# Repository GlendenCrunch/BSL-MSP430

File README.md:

# BSL MSP430 + ftdi-rs232
+ Scheme and PCB of the adapter USB-FTDI to interface RS-232 and bootloader (BSL) for microcontrollers Texas Instrument MSP430
+ Libraries Eagle: SparkFun
+ For MAX232CPE from China capacitor С6 = 48 uF, otherwise it is not needed
+ Package 3D:

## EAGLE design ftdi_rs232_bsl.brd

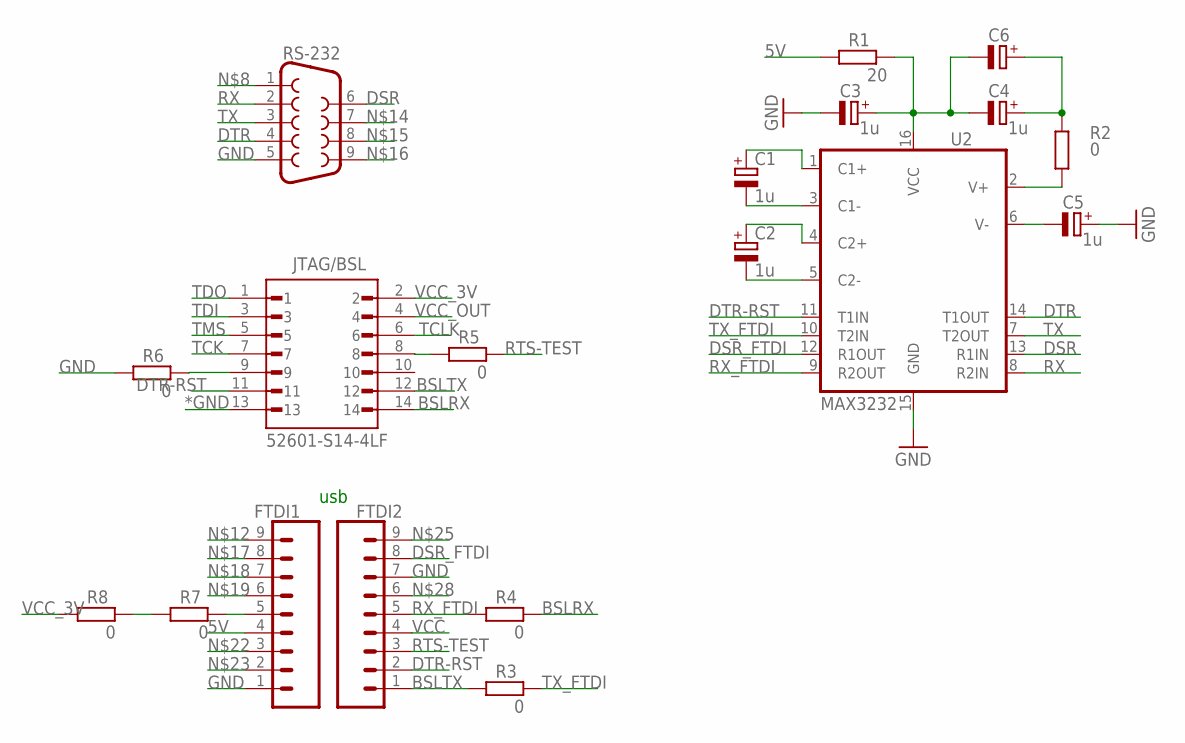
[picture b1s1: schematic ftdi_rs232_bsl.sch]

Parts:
C1, C2, C3, C4, C5: 1u; B/3528-21W
C6: CPOL-EUB/3528-21W; B/3528-21W
FTDI1, FTDI2: CONN_09NO_SILK; 1X09_NO_SILK
JTAG/BSL: 52601-S14-4LF; AMPHENOL_52601-S14-4LF
R1: 20; R1206
R2, R3, R4, R5, R6, R7, R8: 0; R1206
RS-232: DB9MALE; DB9_MALE
U2: MAX3232; DIP16

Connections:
5V: FTDI1.4, R1.1
*GND: JTAG/BSL.13
BSLRX: JTAG/BSL.14, R4.2
BSLTX: FTDI2.1, JTAG/BSL.12, R3.1
DSR: RS-232.6, U2.13 (R1IN)
DSR_FTDI: FTDI2.8, U2.12 (R1OUT)
DTR: RS-232.4, U2.14 (T1OUT)
DTR-RST: FTDI2.2, JTAG/BSL.11, U2.11 (T1IN)
GND: C3.-, C5.+, FTDI1.1, FTDI2.7, R6.1, RS-232.5, U2.15 (GND)
unnamed: C1.-, U2.3 (C1-)
unnamed: C2.-, U2.5 (C2-)
unnamed: C1.+, U2.1 (C1+)
unnamed: C2.+, U2.4 (C2+)
unnamed: C3.+, C4.-, C6.-, R1.2, U2.16 (VCC)
unnamed: C5.-, U2.6 (V-)
unnamed: C4.+, C6.+, R2.2
unnamed: R2.1, U2.2 (V+)
unnamed: JTAG/BSL.8, R5.1
unnamed: JTAG/BSL.9, R6.2
unnamed: FTDI1.5, R7.2
unnamed: R7.1, R8.2
RTS-TEST: FTDI2.3, R5.2
RX: RS-232.2, U2.8 (R2IN)
RX_FTDI: FTDI2.5, R4.1, U2.9 (R2OUT)
TCK: JTAG/BSL.7
TCLK: JTAG/BSL.6
TDI: JTAG/BSL.3
TDO: JTAG/BSL.1
TMS: JTAG/BSL.5
TX: RS-232.3, U2.7 (T2OUT)
TX_FTDI: R3.2, U2.10 (T2IN)
VCC: FTDI2.4
VCC_3V: JTAG/BSL.2, R8.1
VCC_OUT: JTAG/BSL.4

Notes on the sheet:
usb

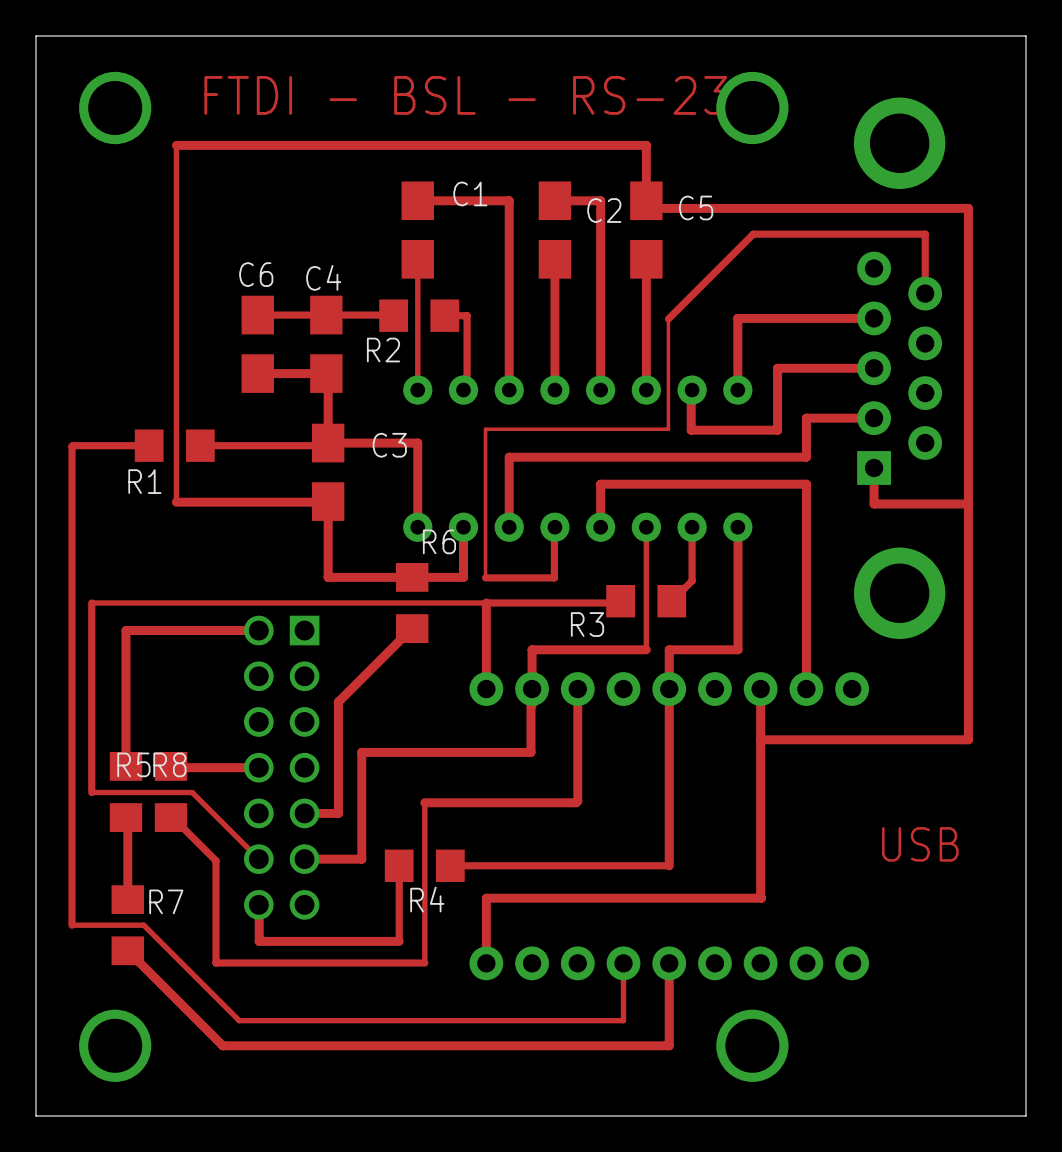
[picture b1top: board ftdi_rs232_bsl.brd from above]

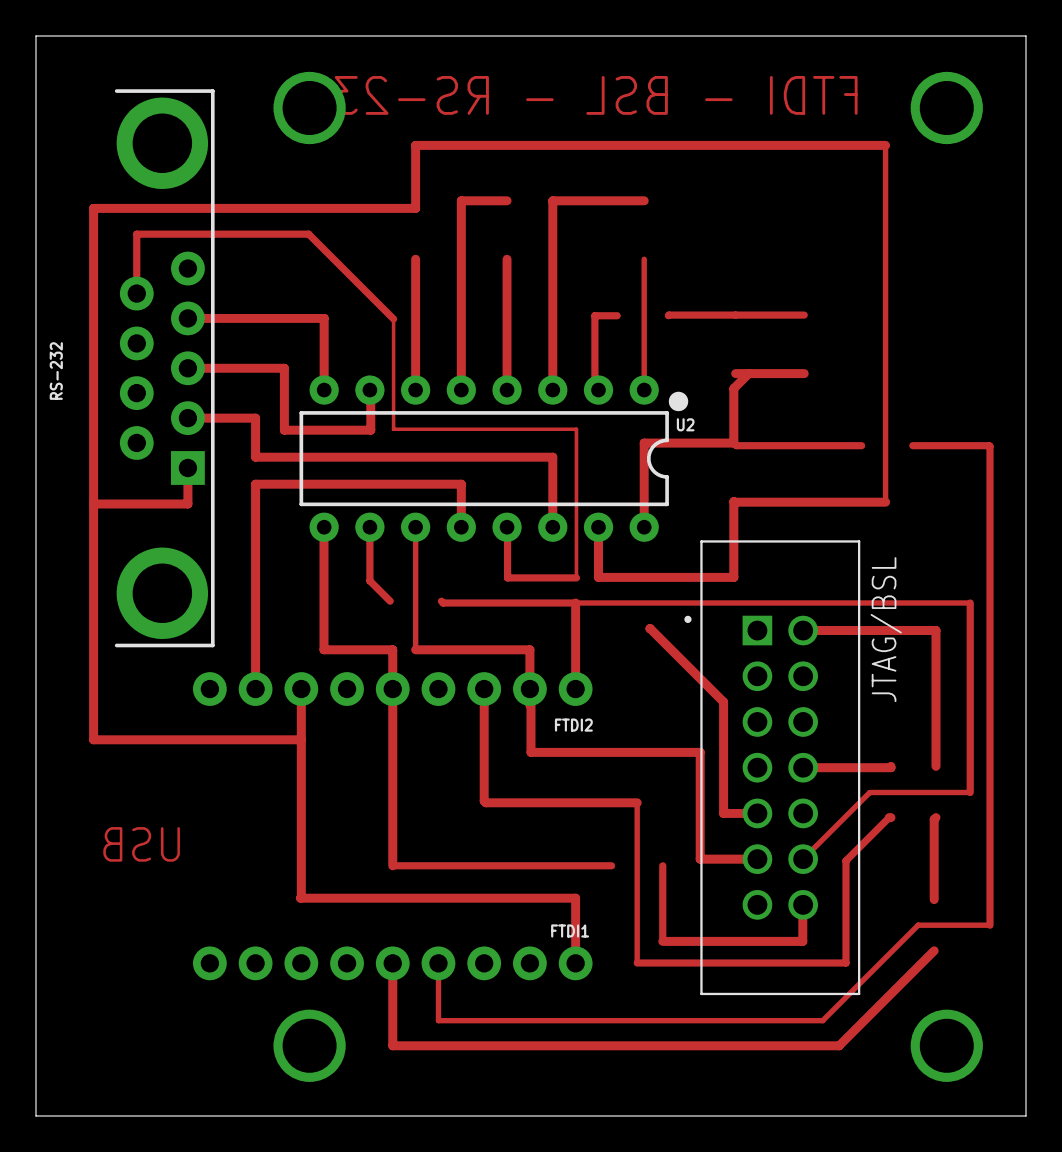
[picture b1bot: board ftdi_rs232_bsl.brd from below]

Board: 2 copper layers, 55.0 x 60.0 mm, 19 parts (5 on the bottom side), 26 nets.

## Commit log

2023-04-09 Create image
2023-04-09 Create 1

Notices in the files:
parts and their libraries:
SparkFun-IC-Comms: Licensing: Creative Commons ShareAlike 4.0 International - https://creativecommons.org/licenses/by-sa/4.0
